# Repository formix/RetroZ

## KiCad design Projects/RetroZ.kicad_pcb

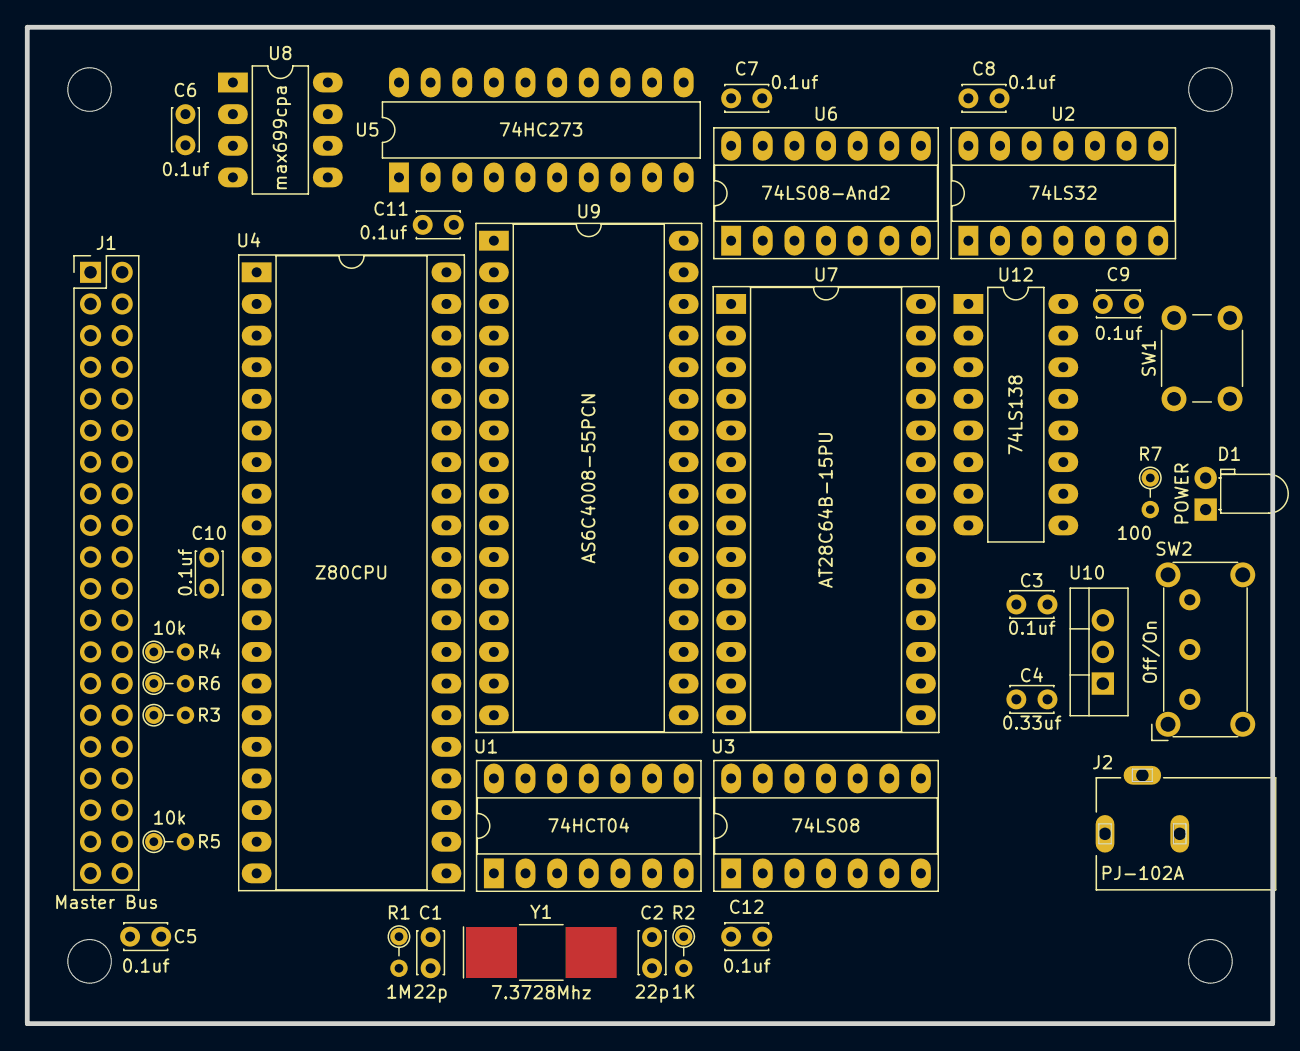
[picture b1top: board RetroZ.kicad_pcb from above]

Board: 4 copper layers, 100.0 x 80.0 mm, 36 parts (0 on the bottom side), 64 nets, no tracks yet.

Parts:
C1, C2: 22p; C_Disc_D3.4mm_W2.1mm_P2.50mm
C3, C5, C6, C7, C8, C9, C10, C11, C12: 0.1uf; C_Disc_D3.4mm_W2.1mm_P2.50mm
C4: 0.33uf; C_Disc_D3.4mm_W2.1mm_P2.50mm
D1: POWER; LED_D3.0mm_Horizontal_O1.27mm_Z2.0mm
J1: Master Bus; Pin_Header_Straight_2x20_Pitch2.54mm
J2: PJ-102A; CUI_PJ-102A
R1: 1M; R_Axial_DIN0204_L3.6mm_D1.6mm_P2.54mm_Vertical
R2: 1K; R_Axial_DIN0204_L3.6mm_D1.6mm_P2.54mm_Vertical
R3, R4, R5, R6: 10k; R_Axial_DIN0204_L3.6mm_D1.6mm_P2.54mm_Vertical
R7: 100; R_Axial_DIN0204_L3.6mm_D1.6mm_P2.54mm_Vertical
SW1: RESET; SW_PUSH_6mm_h5mm
SW2: Off/On; SW_E-Switch_EG1224_SPDT_Angled
U1: 74HCT04; DIP-14_W7.62mm_Socket_LongPads
U2: 74LS32; DIP-14_W7.62mm_Socket_LongPads
U3: 74LS08; DIP-14_W7.62mm_Socket_LongPads
U4: Z80CPU; DIP-40_W15.24mm_Socket_LongPads
U5: 74HC273; DIP-20_W7.62mm_LongPads
U6: 74LS08-And2; DIP-14_W7.62mm_Socket_LongPads
U7: AT28C64B-15PU; DIP-28_W15.24mm_Socket_LongPads
U8: max699cpa; DIP-8_W7.62mm_LongPads
U9: AS6C4008-55PCN; DIP-32_W15.24mm_Socket_LongPads
U10: L7805CV-DG; TO-220-3_Vertical
U12: 74LS138; DIP-16_W7.62mm_LongPads
Y1: 7.3728Mhz; Crystal_SMD_SeikoEpson_MC405-2pin_9.6x4.1mm

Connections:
/A0: J1.1, U4.30, U7.10, U9.12
/A1: J1.2, U4.31, U7.9, U9.11
/A2: J1.3, U4.32, U7.8, U9.10
/A3: J1.4, U4.33, U7.7, U9.9
/A4: J1.5, U4.34, U7.6, U9.8, U12.1
/A5: J1.6, U4.35, U7.5, U9.7, U12.2
/A6: J1.7, U4.36, U7.4, U9.6, U12.3
/A7: J1.8, U4.37, U7.3, U9.5, U12.6
/A8: J1.9, U4.38, U7.25, U9.27
/A9: J1.10, U4.39, U7.24, U9.26
/A10: J1.11, U4.40, U7.21, U9.23
/A11: J1.12, U4.1, U7.23, U9.25
/A12: J1.13, U4.2, U7.2, U9.4
/A13: J1.14, U2.9, U4.3, U9.28
/A14: J1.15, U2.10, U4.4, U9.3
/D0: J1.17, U4.14, U5.3, U7.11, U9.13
/D1: J1.18, U4.15, U5.4, U7.12, U9.14
/D2: J1.19, U4.12, U5.7, U7.13, U9.15
/D3: J1.20, U4.8, U5.8, U7.15, U9.17
/D4: J1.21, U4.7, U5.13, U7.16, U9.18
/D5: J1.22, U4.9, U7.17, U9.19
/D6: J1.23, U4.10, U7.18, U9.20
/D7: J1.24, U4.13, U7.19, U9.21
A15: J1.16, U2.13, U3.5, U4.5
CLK: J1.26, U1.4, U3.2, U4.6
GND: C1.2, C2.2, C3.2, C4.2, C5.2, C6.2, C7.2, C8.2, C9.2, C10.2, C11.2, C12.2, D1.1, J1.40, J2.2, SW1.1, U1.7, U2.7, U3.7, U4.29, U5.10, U5.14, U5.17, U5.18, U6.7, U7.14, U8.3, U8.4, U8.8, U9.16, U10.2, U12.8
unnamed: C1.1, R1.2, U1.1, Y1.1
unnamed: C2.1, R2.2, Y1.2
unnamed: C3.1, SW2.3, U10.3
unnamed: C4.1, J2.1, U10.1
unnamed: D1.2, R7.1
unnamed: R1.1, R2.1, U1.2, U1.3
unnamed: U1.5, U12.15
unnamed: U1.6, U3.1
unnamed: U1.8, U3.10
unnamed: U1.9, U2.11
unnamed: U1.10, U3.9
unnamed: U2.8, U2.12
unnamed: U3.3, U5.11
unnamed: U3.6, U6.2, U6.5, U6.10, U6.13
unnamed: U5.2, U6.1
unnamed: U5.5, U6.4
unnamed: U5.6, U6.9
unnamed: U5.9, U6.12
RAMONLY: U1.11, U3.4, U5.12
RAM_A15: U6.3, U9.31
RAM_A16: U6.6, U9.2
RAM_A17: U6.8, U9.30
RAM_A18: U6.11, U9.1
VCC: C5.1, C6.1, C7.1, C8.1, C9.1, C10.1, C11.1, C12.1, J1.39, R3.2, R4.2, R5.2, R6.2, R7.2, SW2.2, U1.14, U2.14, U3.14, U4.11, U4.17, U5.20, U6.14, U7.27, U7.28, U8.1, U8.2, U9.32, U12.16
~BUSACK: J1.31, U4.23
~BUSREQ: J1.29, R3.1, U4.25
~INT: J1.25, R4.1, U4.16
~IORQ: J1.36, U4.20, U12.4
~M1: J1.33, U4.27
~MRD: U2.3, U7.22, U9.24
~MREQ: J1.34, U2.1, U2.5, U4.19
~MWR: U2.6, U9.29
~RAM_SEL: U1.13, U3.8, U9.22
~RD: J1.30, U2.2, U4.21
~RESET: J1.28, R6.1, SW1.2, U4.26, U5.1, U8.7
~ROM_SEL: U1.12, U7.20
~WAIT: J1.38, R5.1, U4.24
~WR: J1.32, U2.4, U4.22, U12.5
